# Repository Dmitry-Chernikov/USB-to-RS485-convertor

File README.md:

По мотивам этой статьи https://www.rlocman.ru/shem/schematics.html?di=106938

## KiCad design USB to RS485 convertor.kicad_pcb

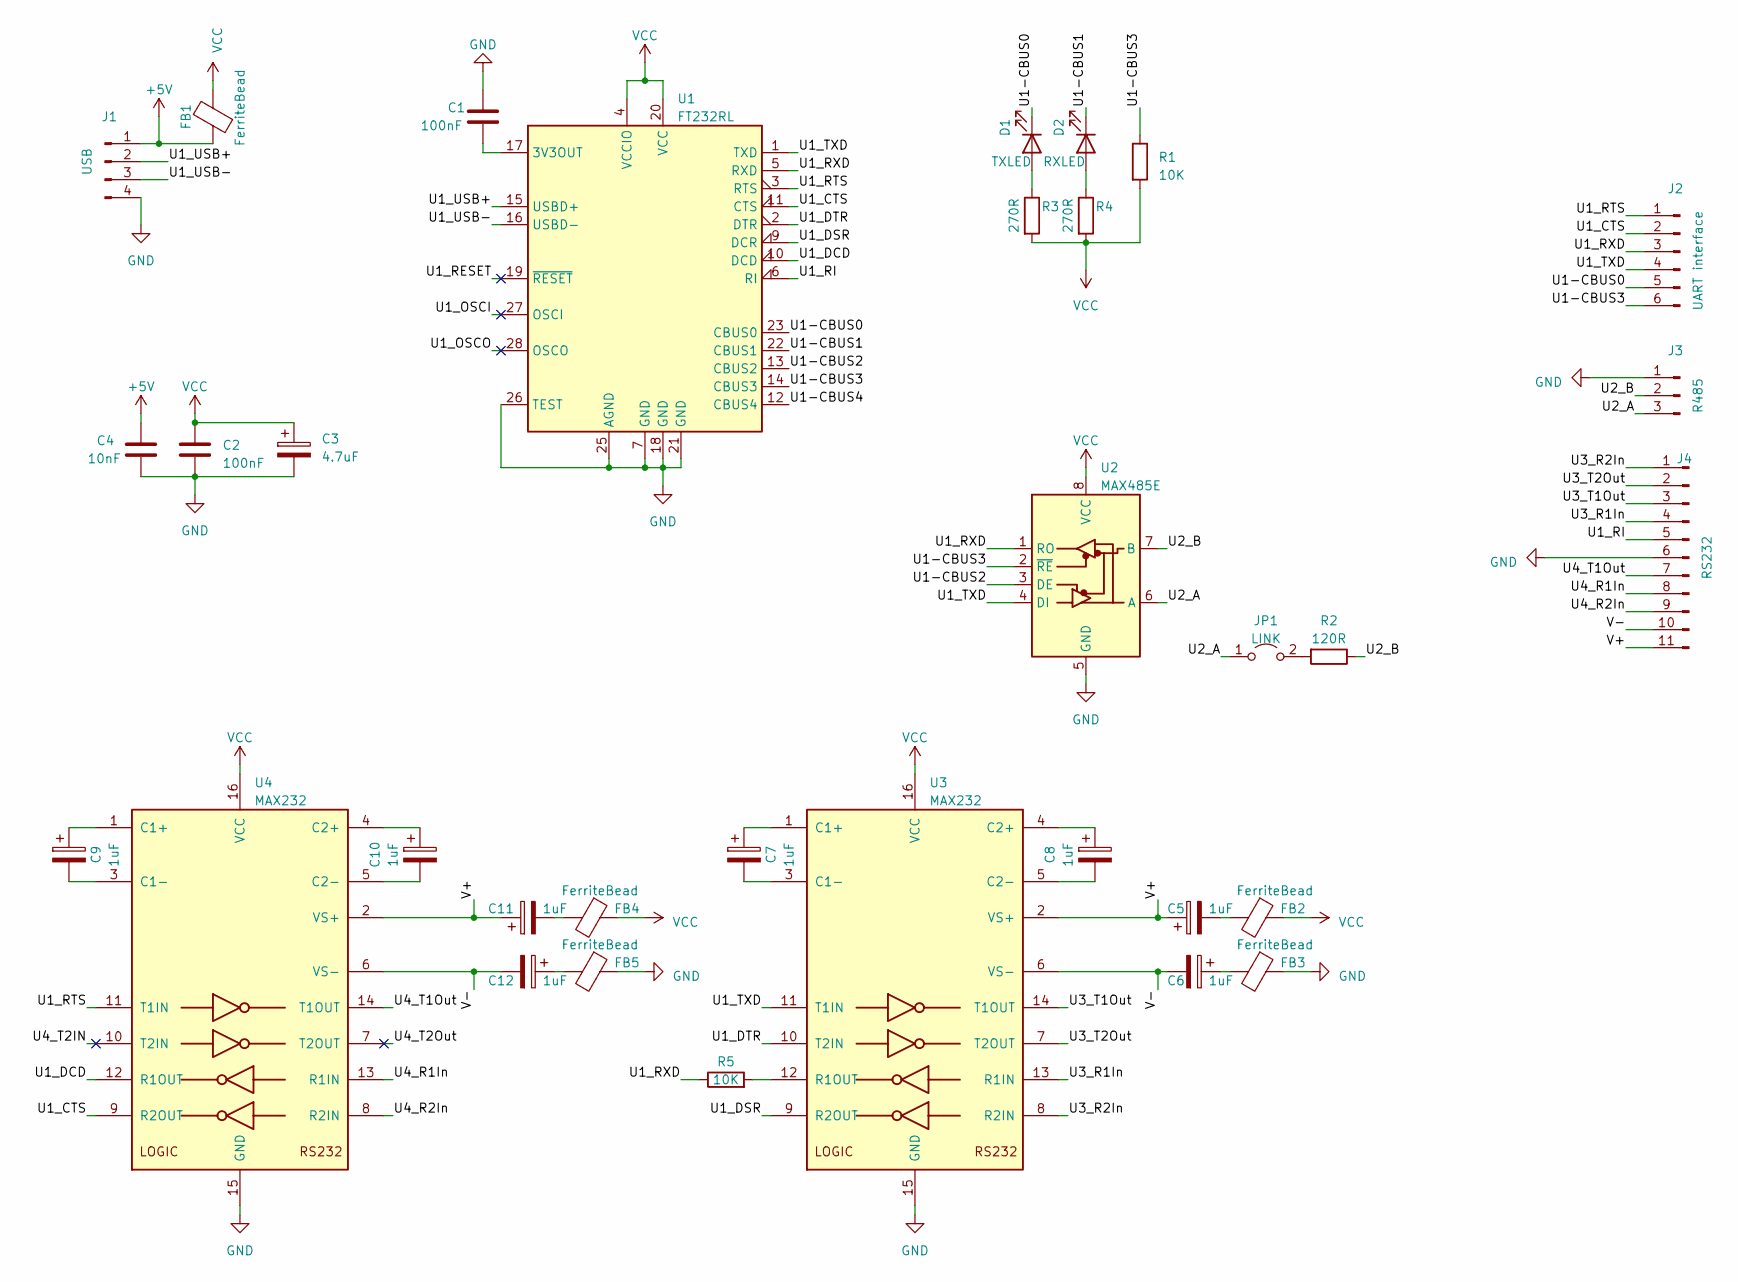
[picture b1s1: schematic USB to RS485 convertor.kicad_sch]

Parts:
C1, C2: 100nF; C_Disc_D4.3mm_W1.9mm_P5.00mm
C3: 4.7uF; CP_Radial_D5.0mm_P2.00mm
C4: 10nF; C_Disc_D5.0mm_W2.5mm_P5.00mm
C5, C6, C7, C8, C9, C10, C11, C12: 1uF; C_Disc_D4.3mm_W1.9mm_P5.00mm
D1: TXLED; LED_D3.0mm
D2: RXLED; LED_D3.0mm
FB1, FB2, FB3, FB4, FB5: FerriteBead; L_0805_2012Metric
J1: USB; PinHeader_1x04_P2.54mm_Vertical
J2: UART interface; PinHeader_1x06_P2.54mm_Vertical
J3: R485; PinHeader_1x03_P2.54mm_Vertical
J4: RS232; PinHeader_1x11_P2.54mm_Vertical
JP1: LINK; PinHeader_1x02_P2.54mm_Vertical
R1, R5: 10K; R_Axial_DIN0207_L6.3mm_D2.5mm_P7.62mm_Horizontal
R2: 120R; R_Axial_DIN0207_L6.3mm_D2.5mm_P7.62mm_Horizontal
R3, R4: 270R; R_Axial_DIN0207_L6.3mm_D2.5mm_P7.62mm_Horizontal
U1: FT232RL; SSOP-28_5.3x10.2mm_P0.65mm
U2: MAX485E; SO-8_3.9x4.9mm_P1.27mm
U3, U4: MAX232; SOIC-16_4.55x10.3mm_P1.27mm

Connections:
+5V: C4.1, FB1.1, J1.1
/U1-CBUS0: D1.1 (K), J2.5, U1.23 (CBUS0)
/U1-CBUS1: D2.1 (K), U1.22 (CBUS1)
/U1-CBUS2: U1.13 (CBUS2), U2.3 (DE)
/U1-CBUS3: J2.6, R1.1, U1.14 (CBUS3), U2.2 (~RE)
/U1-CBUS4: U1.12 (CBUS4)
/U1_CTS: J2.2, U1.11 (CTS), U4.9 (R2OUT)
/U1_DCD: U1.10 (DCD), U4.12 (R1OUT)
/U1_DSR: U1.9 (DCR), U3.9 (R2OUT)
/U1_DTR: U1.2 (DTR), U3.10 (T2IN)
/U1_OSCI: U1.27 (OSCI)
/U1_OSCO: U1.28 (OSCO)
/U1_RESET: U1.19 (~RESET)
/U1_RI: J4.5, U1.6 (RI)
/U1_RTS: J2.1, U1.3 (RTS), U4.11 (T1IN)
/U1_RXD: J2.3, R5.1, U1.5 (RXD), U2.1 (RO)
/U1_TXD: J2.4, U1.1 (TXD), U2.4 (DI), U3.11 (T1IN)
/U1_USB+: J1.2, U1.15 (USBD+)
/U1_USB-: J1.3, U1.16 (USBD-)
/U2_A: J3.3, JP1.1 (A), U2.6 (A)
/U2_B: J3.2, R2.1, U2.7 (B)
/U3_R1In: J4.4, U3.13 (R1IN)
/U3_R2In: J4.1, U3.8 (R2IN)
/U3_T1Out: J4.3, U3.14 (T1OUT)
/U3_T2Out: J4.2, U3.7 (T2OUT)
/U4_R1In: J4.8, U4.13 (R1IN)
/U4_R2In: J4.9, U4.8 (R2IN)
/U4_T1Out: J4.7, U4.14 (T1OUT)
/U4_T2IN: U4.10 (T2IN)
/U4_T2Out: U4.7 (T2OUT)
/V+: C5.1, C11.1, J4.11, U3.2 (VS+), U4.2 (VS+)
/V-: C6.2, C12.2, J4.10, U3.6 (VS-), U4.6 (VS-)
GND: C1.1, C2.2, C3.2, C4.2, FB3.1, FB5.1, J1.4, J3.1, J4.6, U1.7 (GND), U1.18 (GND), U1.21 (GND), U1.25 (AGND), U1.26 (TEST), U2.5 (GND), U3.15 (GND), U4.15 (GND)
unnamed: C5.2, FB2.2
unnamed: C6.1, FB3.2
unnamed: C11.2, FB4.2
unnamed: C12.1, FB5.2
unnamed: D1.2 (A), R3.1
unnamed: D2.2 (A), R4.1
unnamed: JP1.2 (B), R2.2
unnamed: C1.2, U1.17 (3V3OUT)
unnamed: C7.1, U3.1 (C1+)
unnamed: C7.2, U3.3 (C1-)
unnamed: C8.1, U3.4 (C2+)
unnamed: C8.2, U3.5 (C2-)
unnamed: R5.2, U3.12 (R1OUT)
unnamed: C9.1, U4.1 (C1+)
unnamed: C9.2, U4.3 (C1-)
unnamed: C10.1, U4.4 (C2+)
unnamed: C10.2, U4.5 (C2-)
VCC: C2.1, C3.1, FB1.2, FB2.1, FB4.1, R1.2, R3.2, R4.2, U1.4 (VCCIO), U1.20 (VCC), U2.8 (VCC), U3.16 (VCC), U4.16 (VCC)

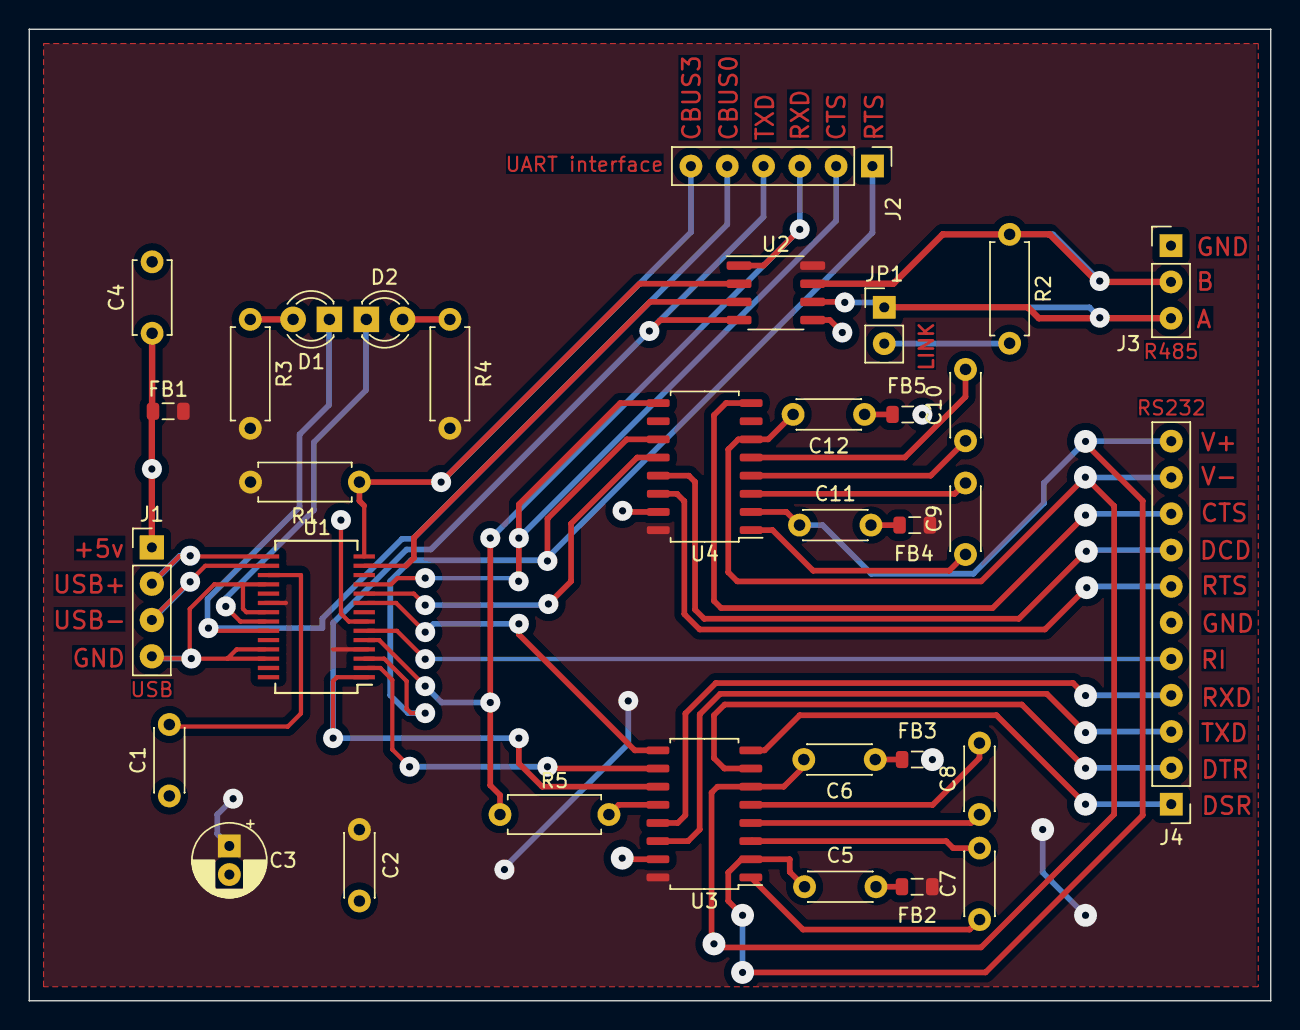
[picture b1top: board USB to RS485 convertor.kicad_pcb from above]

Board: 2 copper layers, 86.9 x 68.0 mm, 33 parts (0 on the bottom side), 45 nets.

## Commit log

2023-09-03 Update README.md
    дескрипшн
2023-09-03 еще раз
2023-09-03 еще раз 2
